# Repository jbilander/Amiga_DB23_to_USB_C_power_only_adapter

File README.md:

# Amiga_DB23_to_USB_C_power_only_adapter
Amiga +5V from external D-sub DB23 floppy drive port to USB Receptacle Type C

***

<br />

<br />

<br />

***

BOM Rev. 1
---------
Designator  | Name/Value   | Package | Notes
-|-|-|-|
J1 | D-Sub DB23 Male connector | EdgeMount, floppy port connector solder type | [DB23M](https://www.networkcables.com/proddetail.php?prod=CO23MS&cat=52)
J2 | USB Type-C Socket SMD DIP Female Jack For PCB | TYPE-C-01 | [TYPE-C-01](https://www.aliexpress.com/item/1005005371954812.html)
C1 | Capacitor Radial Polarized 100uF | 2.5mm pitch, Through-Hole | [100uF 10V](https://www.digikey.com/en/products/detail/nichicon/UHE1A101MDD/589232) <br />Bend down flat to the board surface (in order to fit under shell)
C2 | Capacitor 10uF | 1206 SMD | [1206 10uF X5R 10% 16V](https://www.aliexpress.com/item/33057694240.html)
X | D-Sub DB23 Cover | Two DB23 plastic shells with screws and nuts | [Plastic hood cover x 2](https://www.aliexpress.com/item/1005005014449948.html)

***

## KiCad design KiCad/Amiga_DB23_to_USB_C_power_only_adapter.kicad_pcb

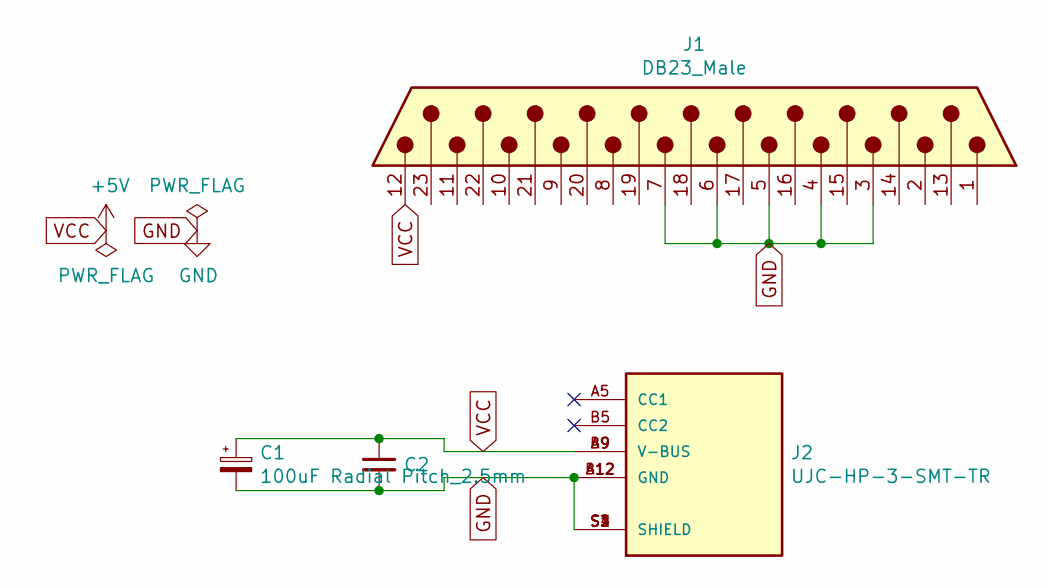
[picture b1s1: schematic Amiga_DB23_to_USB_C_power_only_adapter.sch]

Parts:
C1: 100uF Radial Pitch_2.5mm; CP_Radial_D5.0mm_P2.50mm
C2: C_Small; C_1206_3216Metric_Pad1.42x1.75mm_HandSolder
J1: DB23_Male; DSUB-23_Male_EdgeMount_P2.77mm
J2: UJC-HP-3-SMT-TR; CUI_UJC-HP-3-SMT-TR; PARTREV 04/30/2020

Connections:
GND: C1.2, C2.2, J1.3, J1.4, J1.5, J1.6, J1.7, J2.A12 (GND), J2.B12 (GND), J2.S1 (SHIELD), J2.S2 (SHIELD), J2.S3 (SHIELD), J2.S4 (SHIELD)
VCC: C1.1, C2.1, J1.12, J2.A9 (V-BUS), J2.B9 (V-BUS)

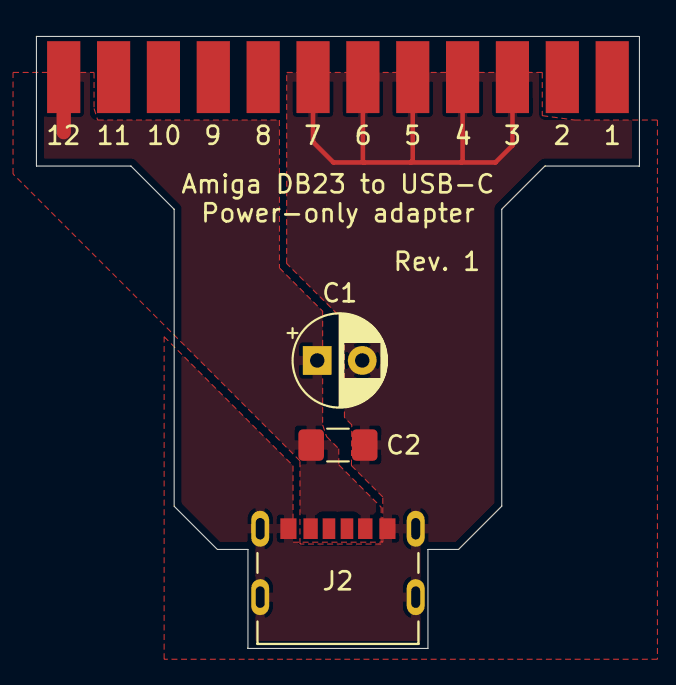
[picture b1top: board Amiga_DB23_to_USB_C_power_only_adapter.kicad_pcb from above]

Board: 2 copper layers, 33.5 x 34.0 mm, 4 parts (0 on the bottom side), 2 nets.

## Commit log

2023-04-12 Create LICENSE
2023-04-14 Added KiCAD files
2023-04-15 Added silkscreen text and OSHW-logo
2023-04-15 Added 3D-model of DB23M
2023-04-15 Added the DB23-plug to the 3D-model and some silkscreen fixes
2023-04-15 Added screenshots
2023-04-17 small fix set gerbers output directory to out/
2023-04-17 Added Rev1 schematic pdf
2023-05-18 Added images
2023-08-13 Added pics

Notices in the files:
KiCad/Amiga_DB23_to_USB_C_power_only_adapter.kicad_pcb:
(C) 2023
